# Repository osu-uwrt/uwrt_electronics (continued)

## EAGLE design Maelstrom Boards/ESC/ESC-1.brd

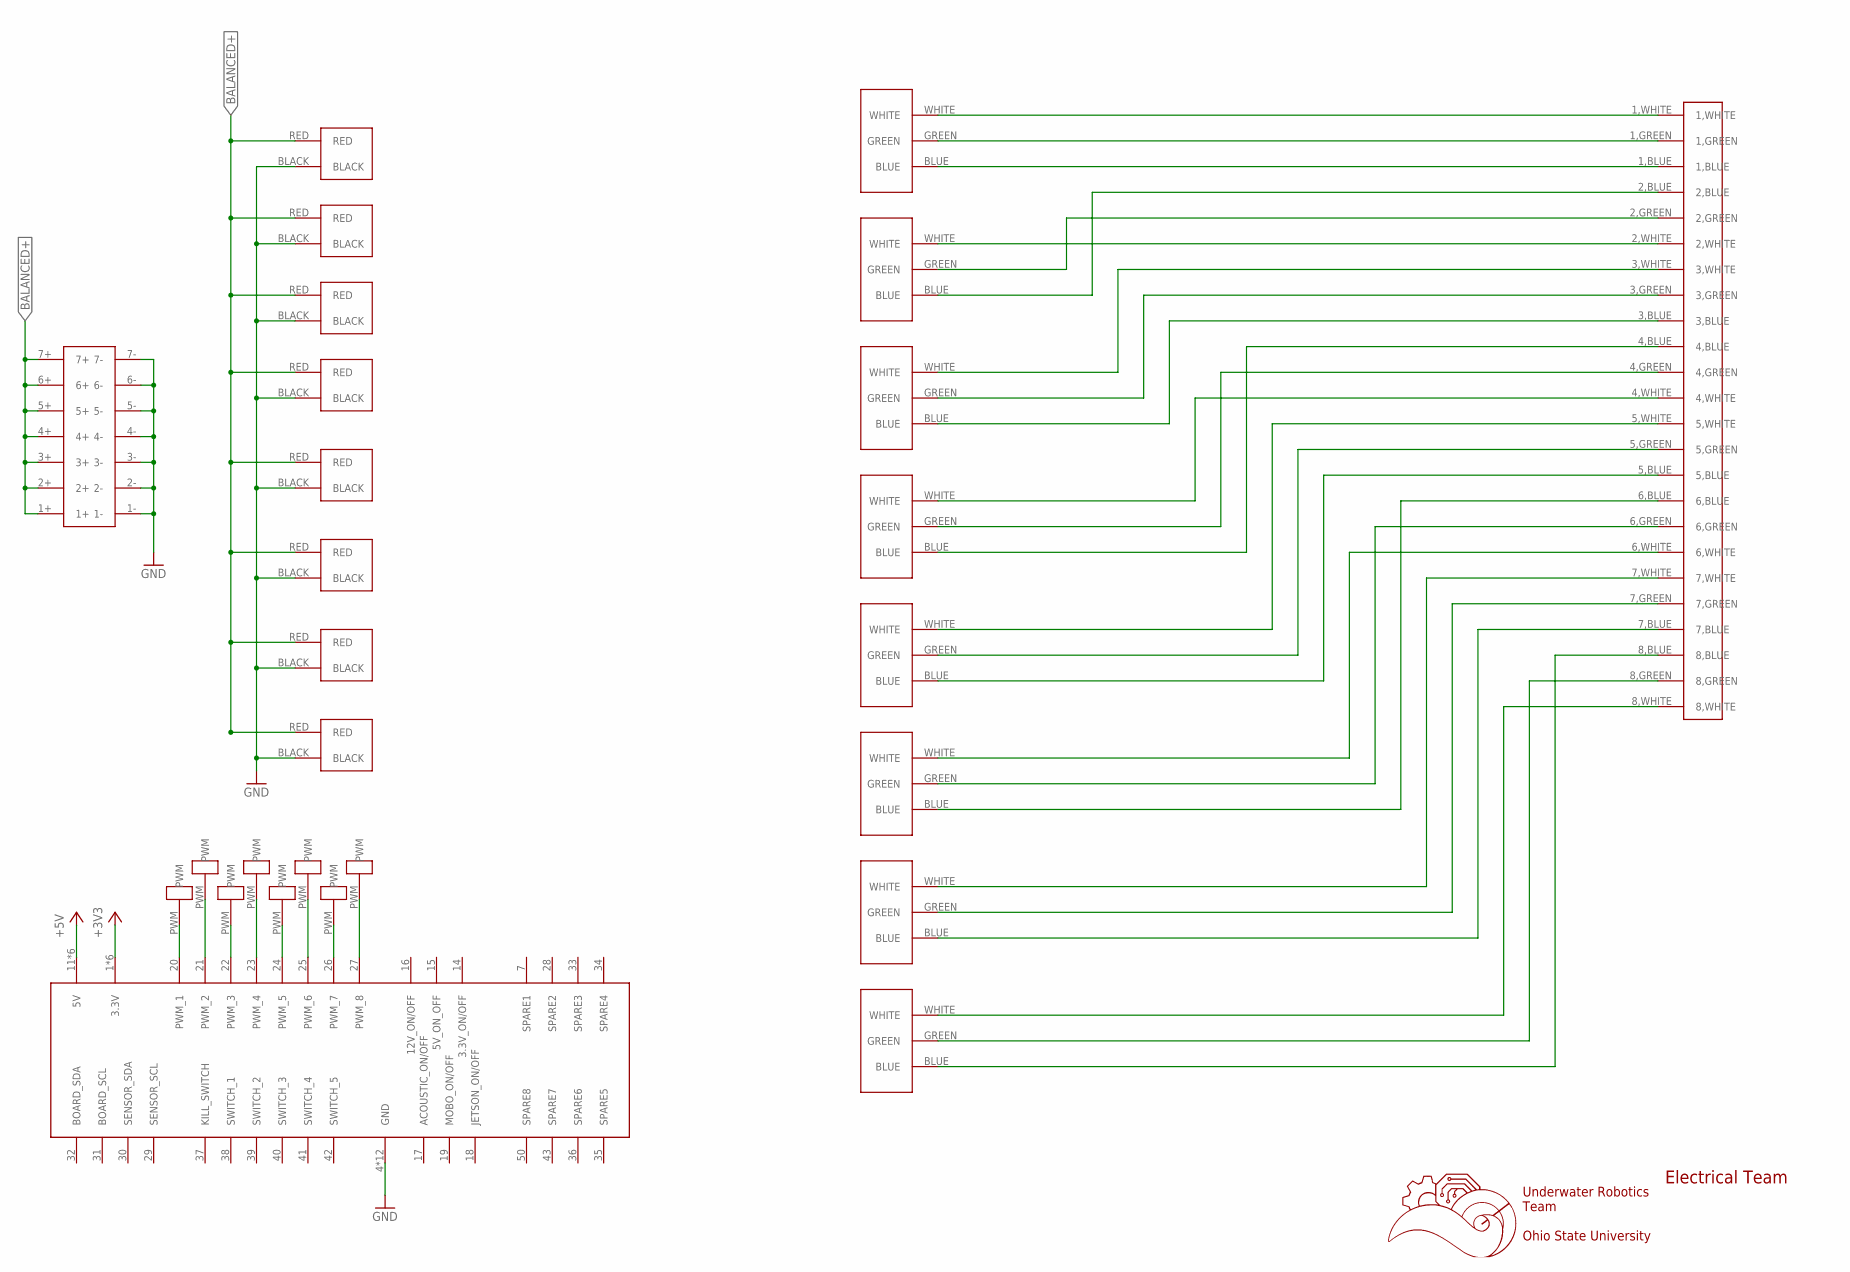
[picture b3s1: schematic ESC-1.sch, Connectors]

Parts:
1, 2, 3, 4, 5, 6, 7, 8: 1711738
U$1: 5530843-EDGE; 5530843-6-BOARDFINGERS
U$2, U$3, U$4, U$5, U$6, U$7, U$8, U$9: 1711725
U$18: 24PINCONVERTER
U$19: 14PIN_VERT
U$20, U$21, U$22, U$23, U$24, U$25, U$26, U$27: MALE1PINHEADER

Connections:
+3V3: U$1.1 (3.3V), U$1.2 (3.3V), U$1.3 (3.3V), U$1.54 (3.3V), U$1.55 (3.3V), U$1.56 (3.3V)
+5V: U$1.11 (5V), U$1.12 (5V), U$1.13 (5V), U$1.44 (5V), U$1.45 (5V), U$1.46 (5V)
BALANCED+: U$2.RED, U$3.RED, U$4.RED, U$5.RED, U$6.RED, U$7.RED, U$8.RED, U$9.RED, U$19.1+, U$19.2+, U$19.3+, U$19.4+, U$19.5+, U$19.6+, U$19.7+
GND: U$1.4 (GND), U$1.5 (GND), U$1.6 (GND), U$1.8 (GND), U$1.9 (GND), U$1.10 (GND), U$1.47 (GND), U$1.48 (GND), U$1.49 (GND), U$1.51 (GND), U$1.52 (GND), U$1.53 (GND), U$2.BLACK, U$3.BLACK, U$4.BLACK, U$5.BLACK, U$6.BLACK, U$7.BLACK, U$8.BLACK, U$9.BLACK, U$19.1-, U$19.2-, U$19.3-, U$19.4-, U$19.5-, U$19.6-, U$19.7-
unnamed: 1.WHITE, U$18.1,WHITE
unnamed: 1.GREEN, U$18.1,GREEN
unnamed: 1.BLUE, U$18.1,BLUE
unnamed: 2.WHITE, U$18.2,WHITE
unnamed: 2.GREEN, U$18.2,GREEN
unnamed: 2.BLUE, U$18.2,BLUE
unnamed: 3.WHITE, U$18.3,WHITE
unnamed: 3.GREEN, U$18.3,GREEN
unnamed: 3.BLUE, U$18.3,BLUE
unnamed: 4.WHITE, U$18.4,WHITE
unnamed: 4.GREEN, U$18.4,GREEN
unnamed: 4.BLUE, U$18.4,BLUE
unnamed: 5.WHITE, U$18.5,WHITE
unnamed: 5.GREEN, U$18.5,GREEN
unnamed: 5.BLUE, U$18.5,BLUE
unnamed: 6.BLUE, U$18.6,BLUE
unnamed: 6.WHITE, U$18.6,WHITE
unnamed: 6.GREEN, U$18.6,GREEN
unnamed: 7.WHITE, U$18.7,WHITE
unnamed: 7.GREEN, U$18.7,GREEN
unnamed: 7.BLUE, U$18.7,BLUE
unnamed: 8.WHITE, U$18.8,WHITE
unnamed: 8.GREEN, U$18.8,GREEN
unnamed: 8.BLUE, U$18.8,BLUE
PWM_1: U$1.20 (PWM_1), U$20.PWM
PWM_2: U$1.21 (PWM_2), U$21.PWM
PWM_3: U$1.22 (PWM_3), U$22.PWM
PWM_4: U$1.23 (PWM_4), U$23.PWM
PWM_5: U$1.24 (PWM_5), U$24.PWM
PWM_6: U$1.25 (PWM_6), U$25.PWM
PWM_7: U$1.26 (PWM_7), U$26.PWM
PWM_8: U$1.27 (PWM_8), U$27.PWM

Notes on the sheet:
Underwater Robotics Team Ohio State University
Electrical Team

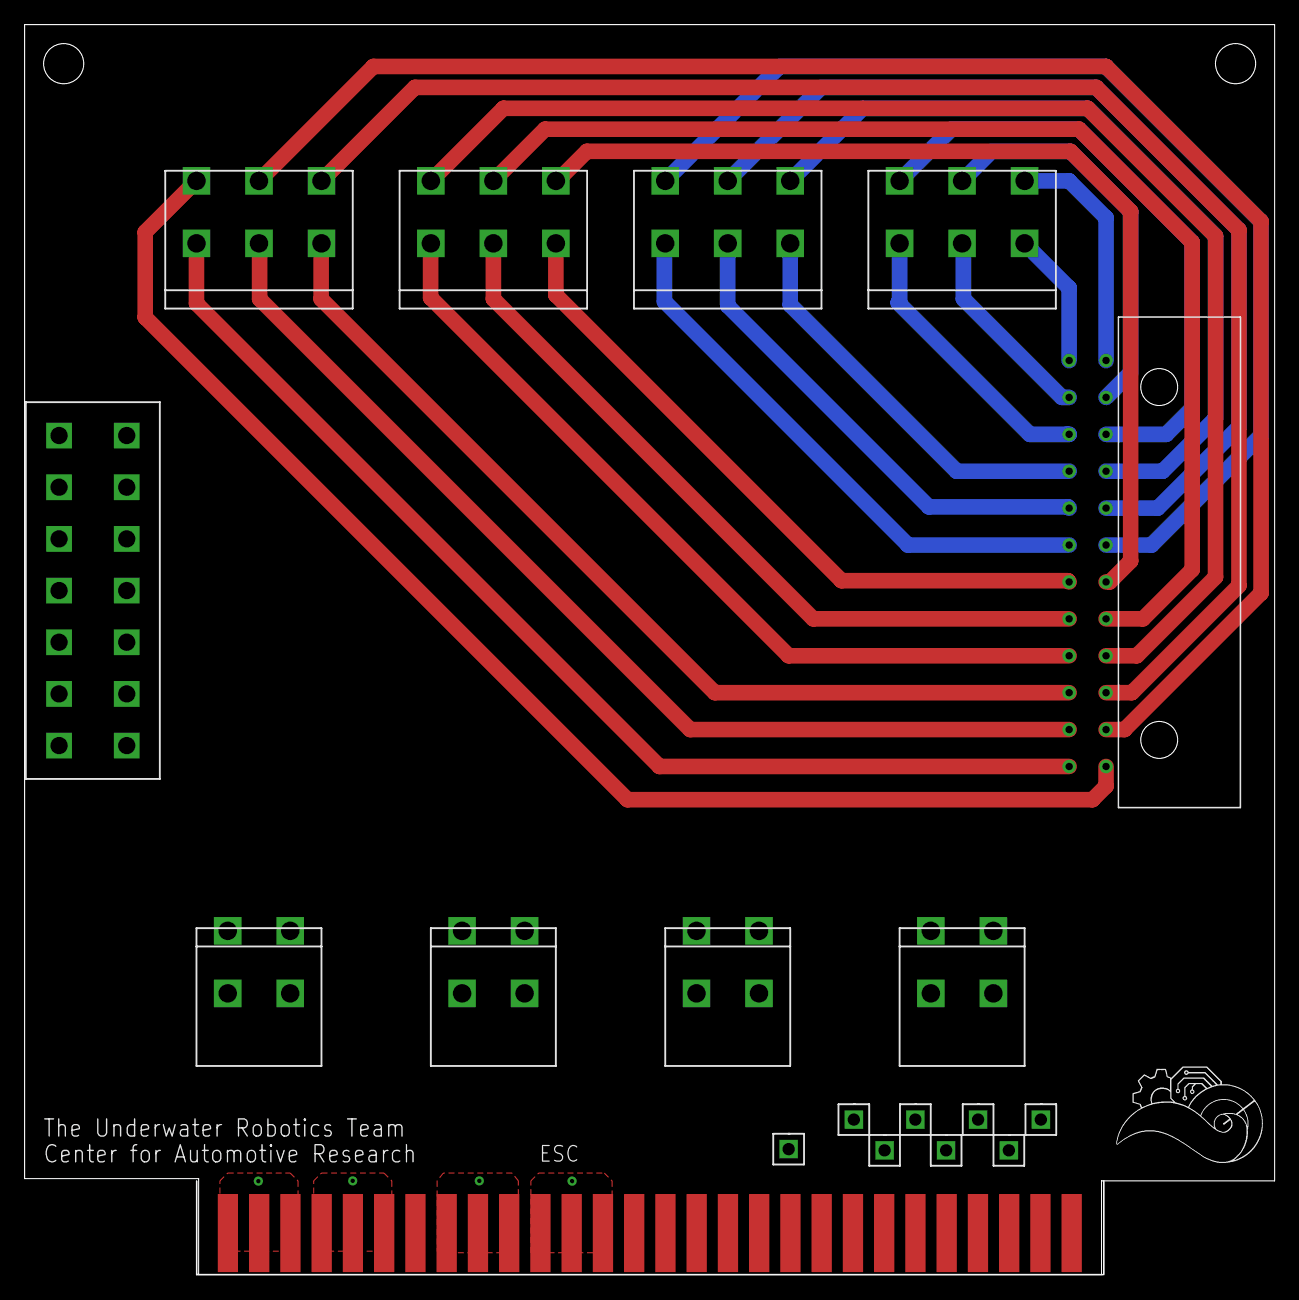
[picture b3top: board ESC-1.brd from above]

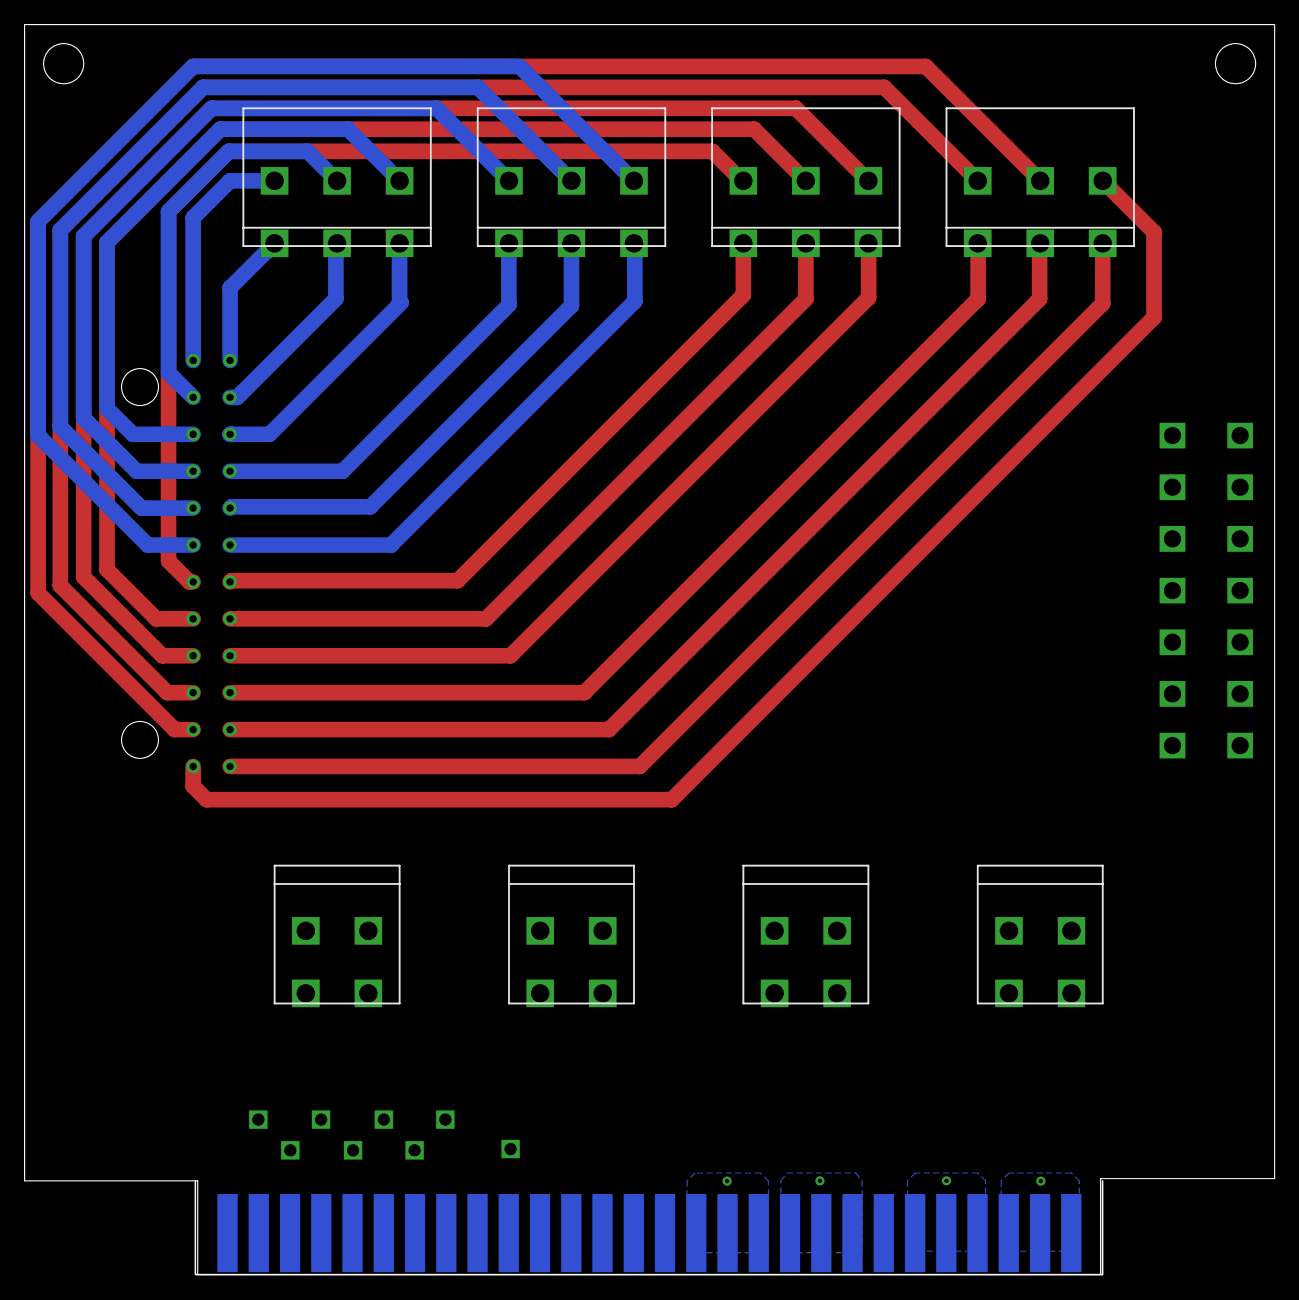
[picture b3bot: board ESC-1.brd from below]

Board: 2 copper layers, 101.6 x 101.6 mm, 27 parts (8 on the bottom side), 36 nets.

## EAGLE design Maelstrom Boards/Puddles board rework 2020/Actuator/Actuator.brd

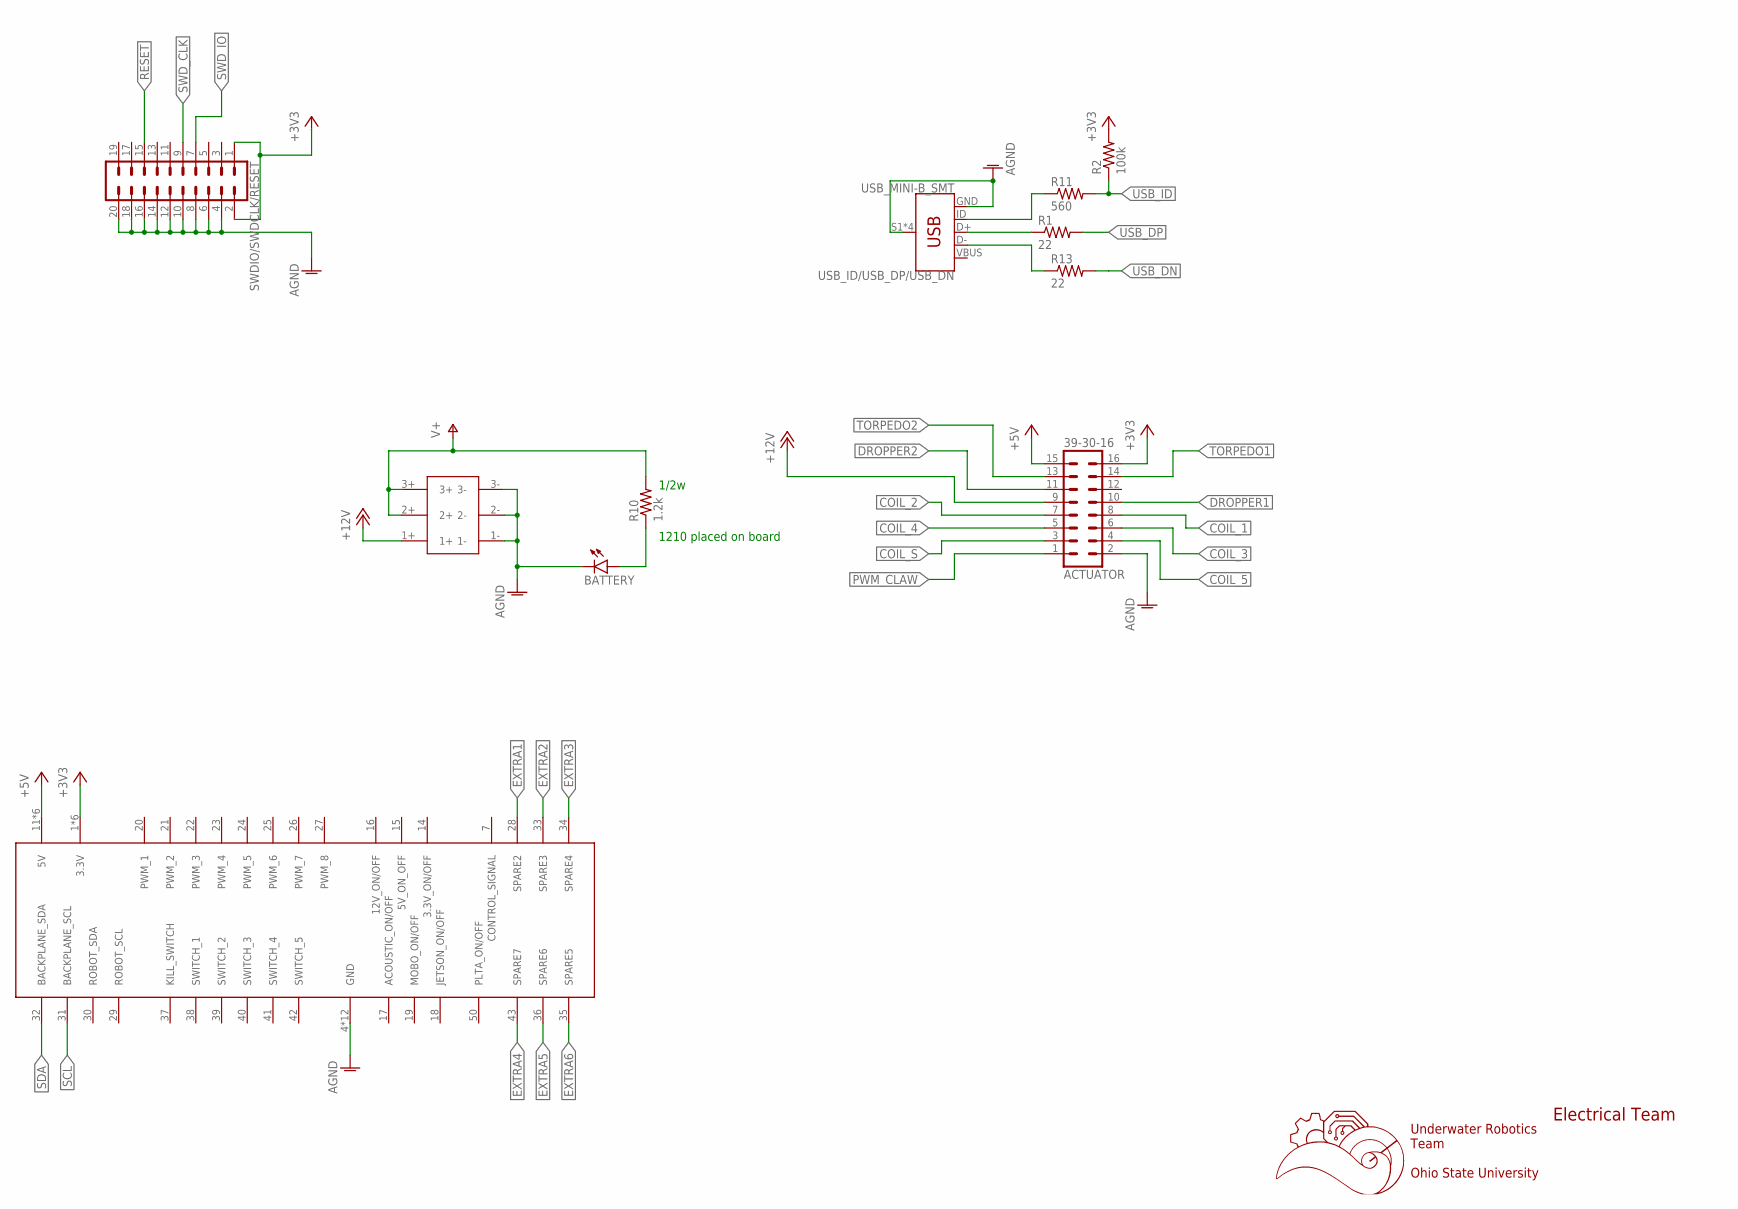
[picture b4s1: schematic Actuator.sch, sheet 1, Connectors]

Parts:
ACTUATOR: 39-30-16; 39-30-?16?
BATTERY: LEDCHIPLED_0603; CHIPLED_0603
R1, R13: 22; R0603
R2: 100k; R0603
R10: 1.2k; R1210
R11: 560; R0603
SWDIO/SWDCLK/RESET: CONN_10X2; 2X10
U$1: 5530843-EDGE; 5530843-6-BOARDFINGERS
U$3: 6PIN-VERT; 6PIN_VERT
USB_ID/USB_DP/USB_DN: USB_MINI-B_SMT; USB-MINIB

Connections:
+3V3: ACTUATOR.16, R2.2, SWDIO/SWDCLK/RESET.1, SWDIO/SWDCLK/RESET.2, U$1.1 (3.3V), U$1.2 (3.3V), U$1.3 (3.3V), U$1.54 (3.3V), U$1.55 (3.3V), U$1.56 (3.3V); also elsewhere on the board
+5V: ACTUATOR.15, U$1.11 (5V), U$1.12 (5V), U$1.13 (5V), U$1.44 (5V), U$1.45 (5V), U$1.46 (5V)
+12V: ACTUATOR.9, U$3.1+; also elsewhere on the board
AGND: ACTUATOR.2, BATTERY.C, SWDIO/SWDCLK/RESET.4, SWDIO/SWDCLK/RESET.6, SWDIO/SWDCLK/RESET.8, SWDIO/SWDCLK/RESET.10, SWDIO/SWDCLK/RESET.12, SWDIO/SWDCLK/RESET.14, SWDIO/SWDCLK/RESET.16, SWDIO/SWDCLK/RESET.18, SWDIO/SWDCLK/RESET.20, U$1.4 (GND), U$1.5 (GND), U$1.6 (GND), U$1.8 (GND), U$1.9 (GND), U$1.10 (GND), U$1.47 (GND), U$1.48 (GND), U$1.49 (GND), U$1.51 (GND), U$1.52 (GND), U$1.53 (GND), U$3.1-, U$3.2-, U$3.3-, USB_ID/USB_DP/USB_DN.GND, USB_ID/USB_DP/USB_DN.S1 (SHIELD), USB_ID/USB_DP/USB_DN.S2 (SHIELD), USB_ID/USB_DP/USB_DN.S3 (SHIELD), USB_ID/USB_DP/USB_DN.S4 (SHIELD); also elsewhere on the board
COIL_1: ACTUATOR.8; also elsewhere on the board
COIL_2: ACTUATOR.7; also elsewhere on the board
COIL_3: ACTUATOR.6; also elsewhere on the board
COIL_4: ACTUATOR.5; also elsewhere on the board
COIL_5: ACTUATOR.4; also elsewhere on the board
COIL_S: ACTUATOR.3; also elsewhere on the board
DROPPER1: ACTUATOR.10; also elsewhere on the board
DROPPER2: ACTUATOR.11; also elsewhere on the board
EXTRA1: U$1.28 (SPARE2); also elsewhere on the board
EXTRA2: U$1.33 (SPARE3); also elsewhere on the board
EXTRA3: U$1.34 (SPARE4); also elsewhere on the board
EXTRA4: U$1.43 (SPARE7); also elsewhere on the board
EXTRA5: U$1.36 (SPARE6); also elsewhere on the board
EXTRA6: U$1.35 (SPARE5); also elsewhere on the board
unnamed: R11.1, USB_ID/USB_DP/USB_DN.ID
unnamed: R1.1, USB_ID/USB_DP/USB_DN.D+
unnamed: R13.1, USB_ID/USB_DP/USB_DN.D-
unnamed: BATTERY.A, R10.1
PWM_CLAW: ACTUATOR.1; also elsewhere on the board
RESET: SWDIO/SWDCLK/RESET.15; also elsewhere on the board
SCL: U$1.31 (BACKPLANE_SCL); also elsewhere on the board
SDA: U$1.32 (BACKPLANE_SDA); also elsewhere on the board
SWD_CLK: SWDIO/SWDCLK/RESET.9; also elsewhere on the board
SWD_IO: SWDIO/SWDCLK/RESET.7; also elsewhere on the board
TORPEDO1: ACTUATOR.14; also elsewhere on the board
TORPEDO2: ACTUATOR.13; also elsewhere on the board
USB_DN: R13.2; also elsewhere on the board
USB_DP: R1.2; also elsewhere on the board
USB_ID: R2.1, R11.2
V+: R10.2, U$3.2+, U$3.3+; also elsewhere on the board
VBUS: USB_ID/USB_DP/USB_DN.VBUS

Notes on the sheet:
Underwater Robotics Team Ohio State University
Electrical Team
1/2w
1210 placed on board

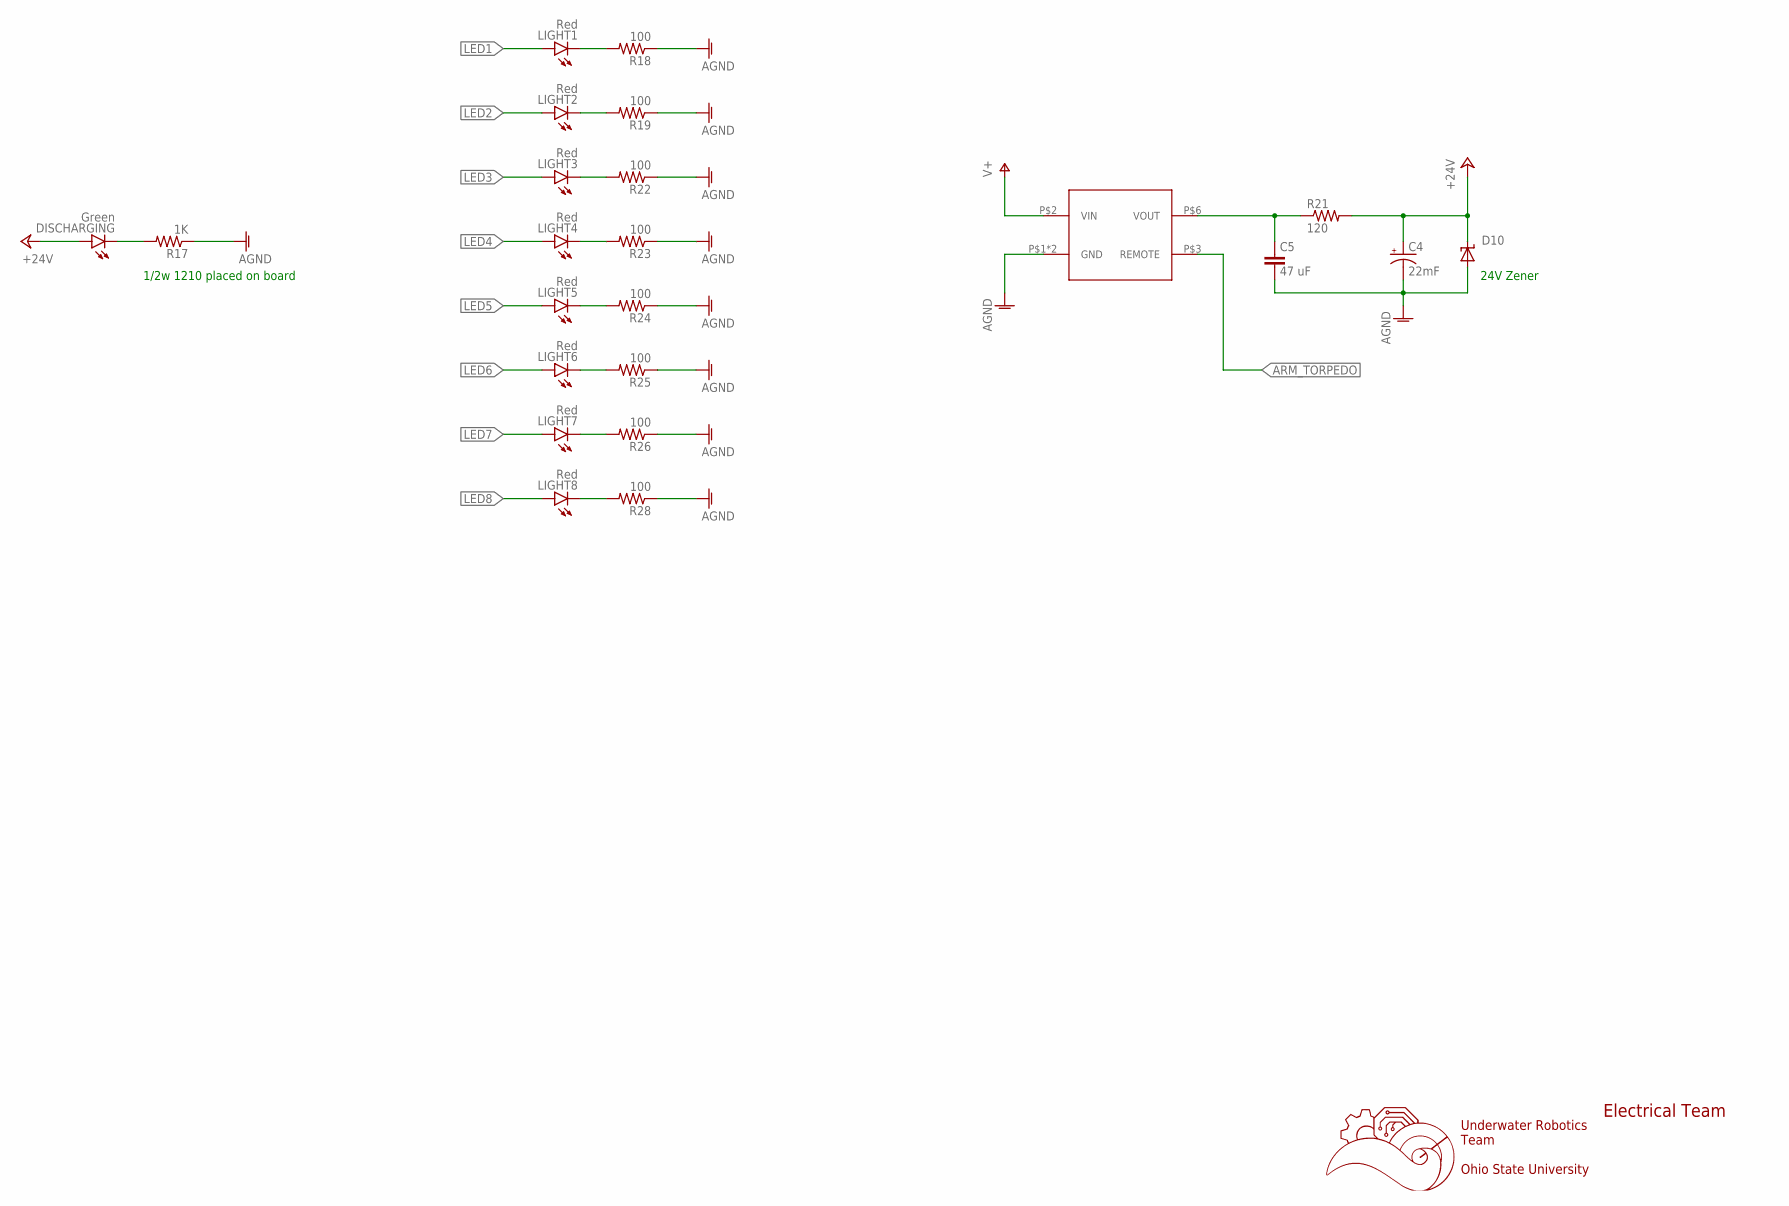
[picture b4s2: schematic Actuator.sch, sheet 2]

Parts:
C4: 22mF; EB30D
C5: 47 uF; C0603
D10: SUPPRESSOR-SMBJ; SMBJ
DISCHARGING: Green; CHIPLED_0603
LIGHT1, LIGHT2, LIGHT3, LIGHT4, LIGHT5, LIGHT6, LIGHT7, LIGHT8: Red; CHIPLED_0603
R17: 1K; R1210
R18, R19, R22, R23, R24, R25, R26, R28: 100; R0603
R21: 120; R6332W
U$6: TMR6-2415

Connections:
+24V: C4.+, D10.C, DISCHARGING.A, R21.2; also elsewhere on the board
AGND: C4.-, C5.2, D10.A, R17.1, R18.1, R19.1, R22.1, R23.1, R24.1, R25.1, R26.1, R28.1, U$6.P$1 (GND), U$6.P$7 (GND); also elsewhere on the board
ARM_TORPEDO: U$6.P$3 (REMOTE); also elsewhere on the board
LED1: LIGHT1.A; also elsewhere on the board
LED2: LIGHT2.A; also elsewhere on the board
LED3: LIGHT3.A; also elsewhere on the board
LED4: LIGHT4.A; also elsewhere on the board
LED5: LIGHT5.A; also elsewhere on the board
LED6: LIGHT6.A; also elsewhere on the board
LED7: LIGHT7.A; also elsewhere on the board
LED8: LIGHT8.A; also elsewhere on the board
unnamed: DISCHARGING.C, R17.2
unnamed: LIGHT1.C, R18.2
unnamed: LIGHT2.C, R19.2
unnamed: LIGHT3.C, R22.2
unnamed: LIGHT4.C, R23.2
unnamed: LIGHT5.C, R24.2
unnamed: LIGHT6.C, R25.2
unnamed: LIGHT7.C, R26.2
unnamed: LIGHT8.C, R28.2
unnamed: C5.1, R21.1, U$6.P$6 (VOUT)
V+: U$6.P$2 (VIN); also elsewhere on the board

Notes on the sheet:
Underwater Robotics Team Ohio State University
Electrical Team
24V Zener
1/2w 1210 placed on board

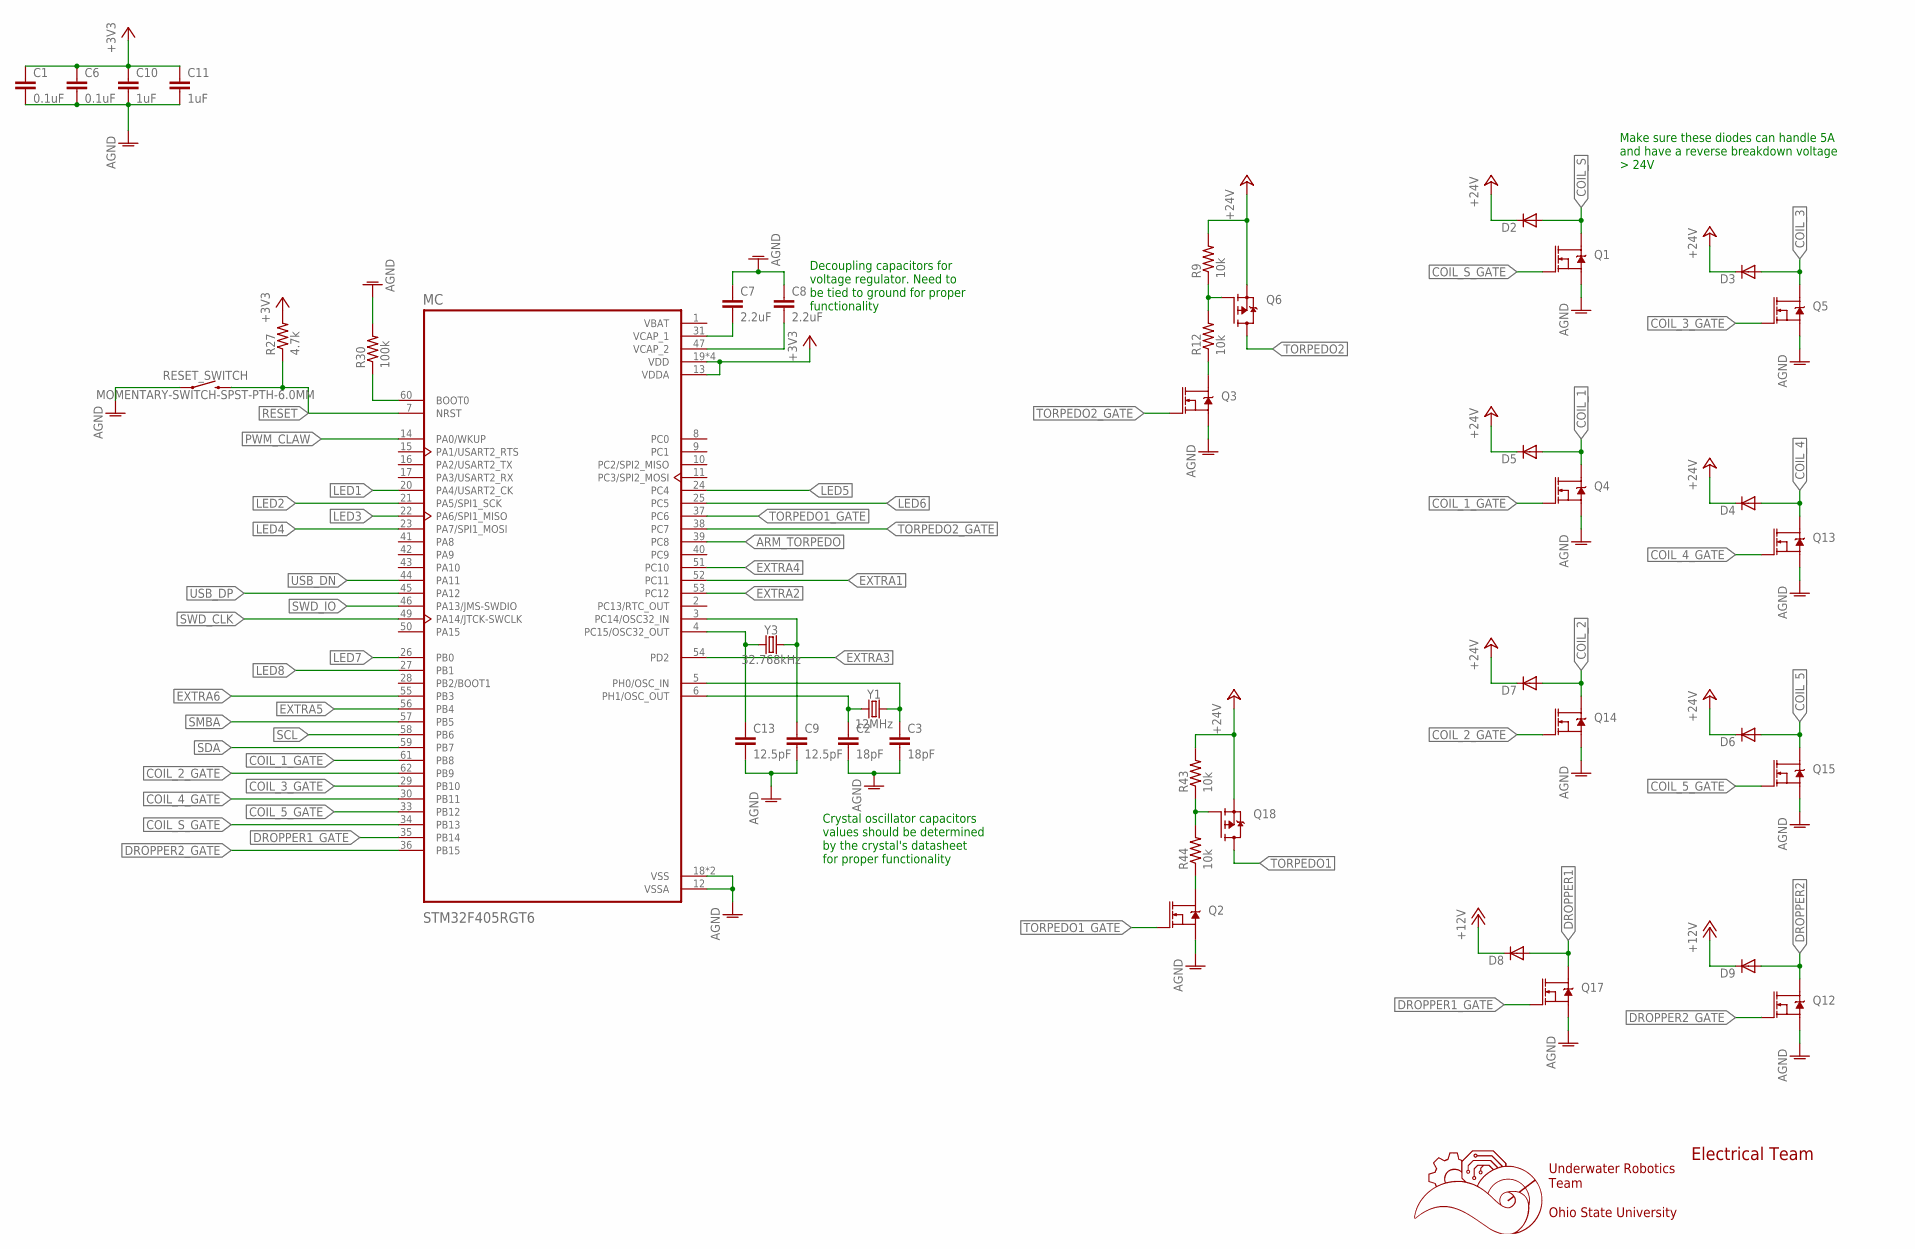
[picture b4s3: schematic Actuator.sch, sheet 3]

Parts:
C1, C6: 0.1uF; C0603
C2, C3: 18pF; C0603
C7, C8: 2.2uF; C0603
C9, C13: 12.5pF; C0603
C10, C11: 1uF; C0603
D2, D3, D4, D5, D6, D7, D8, D9: DIODE-SMB; SMB
MC: STM32F405RGT6; QFP50P1200X1200X160-64N
Q1, Q2, Q3, Q4, Q5, Q12, Q13, Q14, Q15, Q17: MOSFET-NCH-AO3404A; SOT23-3
Q6, Q18: FDD4141TO252; TO252
R9, R12, R43, R44: 10k; R0603
R27: 4.7k; R0603
R30: 100k; R0603
RESET_SWITCH: MOMENTARY-SWITCH-SPST-PTH-6.0MM; TACTILE_SWITCH_PTH_6.0MM
Y1: 12MHz; HC49US
Y3: 32.768kHz; CRYSTAL-SMD-3.2X1.5MM

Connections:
+3V3: C1.1, C6.1, C10.1, C11.1, MC.13 (VDDA), MC.19 (VDD), MC.32 (VDD), MC.48 (VDD), MC.64 (VDD), R27.2; also elsewhere on the board
+12V: D8.C, D9.C; also elsewhere on the board
+24V: D2.C, D3.C, D4.C, D5.C, D6.C, D7.C, Q6.2 (S), Q18.2 (S), R9.2, R43.2; also elsewhere on the board
AGND: C1.2, C2.2, C3.2, C6.2, C7.1, C8.1, C9.2, C10.2, C11.2, C13.2, MC.12 (VSSA), MC.18 (VSS), MC.63 (VSS), Q1.2 (S), Q2.2 (S), Q3.2 (S), Q4.2 (S), Q5.2 (S), Q12.2 (S), Q13.2 (S), Q14.2 (S), Q15.2 (S), Q17.2 (S), R30.2, RESET_SWITCH.1; also elsewhere on the board
ARM_TORPEDO: MC.39 (PC8); also elsewhere on the board
COIL_1: D5.A, Q4.3 (D); also elsewhere on the board
COIL_1_GATE: MC.61 (PB8), Q4.1 (G)
COIL_2: D7.A, Q14.3 (D); also elsewhere on the board
COIL_2_GATE: MC.62 (PB9), Q14.1 (G)
COIL_3: D3.A, Q5.3 (D); also elsewhere on the board
COIL_3_GATE: MC.29 (PB10), Q5.1 (G)
COIL_4: D4.A, Q13.3 (D); also elsewhere on the board
COIL_4_GATE: MC.30 (PB11), Q13.1 (G)
COIL_5: D6.A, Q15.3 (D); also elsewhere on the board
COIL_5_GATE: MC.33 (PB12), Q15.1 (G)
COIL_S: D2.A, Q1.3 (D); also elsewhere on the board
COIL_S_GATE: MC.34 (PB13), Q1.1 (G)
DROPPER1: D8.A, Q17.3 (D); also elsewhere on the board
DROPPER1_GATE: MC.35 (PB14), Q17.1 (G)
DROPPER2: D9.A, Q12.3 (D); also elsewhere on the board
DROPPER2_GATE: MC.36 (PB15), Q12.1 (G)
EXTRA1: MC.52 (PC11); also elsewhere on the board
EXTRA2: MC.53 (PC12); also elsewhere on the board
EXTRA3: MC.54 (PD2); also elsewhere on the board
EXTRA4: MC.51 (PC10); also elsewhere on the board
EXTRA5: MC.56 (PB4); also elsewhere on the board
EXTRA6: MC.55 (PB3); also elsewhere on the board
LED1: MC.20 (PA4/USART2_CK); also elsewhere on the board
LED2: MC.21 (PA5/SPI1_SCK); also elsewhere on the board
LED3: MC.22 (PA6/SPI1_MISO); also elsewhere on the board
LED4: MC.23 (PA7/SPI1_MOSI); also elsewhere on the board
LED5: MC.24 (PC4); also elsewhere on the board
LED6: MC.25 (PC5); also elsewhere on the board
LED7: MC.26 (PB0); also elsewhere on the board
LED8: MC.27 (PB1); also elsewhere on the board
unnamed: C2.1, MC.6 (PH1/OSC_OUT), Y1.1
unnamed: C3.1, MC.5 (PH0/OSC_IN), Y1.2
unnamed: C8.2, MC.47 (VCAP_2)
unnamed: C13.1, MC.4 (PC15/OSC32_OUT), Y3.P$1 (1)
unnamed: C7.2, MC.31 (VCAP_1)
unnamed: Q2.3 (D), R44.1
unnamed: Q18.1 (G), R43.1, R44.2
unnamed: Q6.1 (G), R9.1, R12.2
unnamed: Q3.3 (D), R12.1
unnamed: C9.1, MC.3 (PC14/OSC32_IN), Y3.P$2 (2)
unnamed: MC.60 (BOOT0), R30.1
PWM_CLAW: MC.14 (PA0/WKUP); also elsewhere on the board
RESET: MC.7 (NRST), R27.1, RESET_SWITCH.3 (2); also elsewhere on the board
SCL: MC.58 (PB6); also elsewhere on the board
SDA: MC.59 (PB7); also elsewhere on the board
SMBA: MC.57 (PB5)
SWD_CLK: MC.49 (PA14/JTCK-SWCLK); also elsewhere on the board
SWD_IO: MC.46 (PA13/JMS-SWDIO); also elsewhere on the board
TORPEDO1: Q18.3 (D); also elsewhere on the board
TORPEDO1_GATE: MC.37 (PC6), Q2.1 (G)
TORPEDO2: Q6.3 (D); also elsewhere on the board
TORPEDO2_GATE: MC.38 (PC7), Q3.1 (G)
USB_DN: MC.44 (PA11); also elsewhere on the board
USB_DP: MC.45 (PA12); also elsewhere on the board
VBAT: MC.1 (VBAT)

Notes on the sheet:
Underwater Robotics Team Ohio State University
Electrical Team
Decoupling capacitors for voltage regulator. Need to be tied to ground for proper functionality
Crystal oscillator capacitors values should be determined by the crystal's datasheet for proper functionality
Make sure these diodes can handle 5A and have a reverse breakdown voltage > 24V

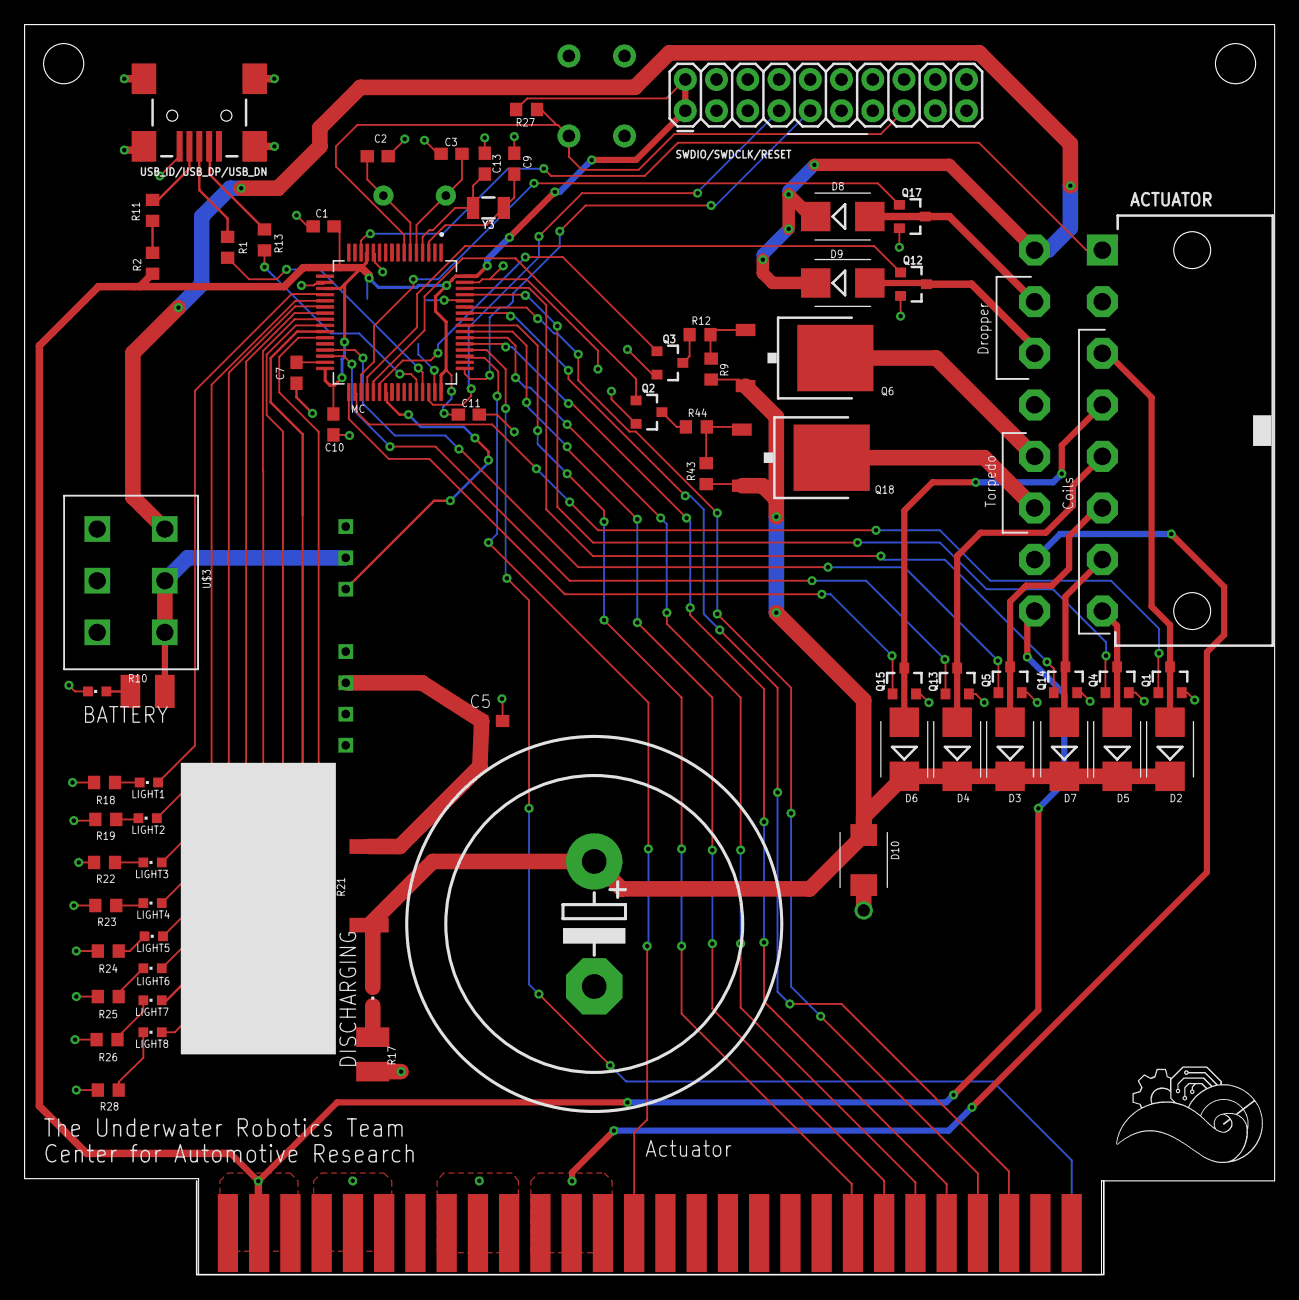
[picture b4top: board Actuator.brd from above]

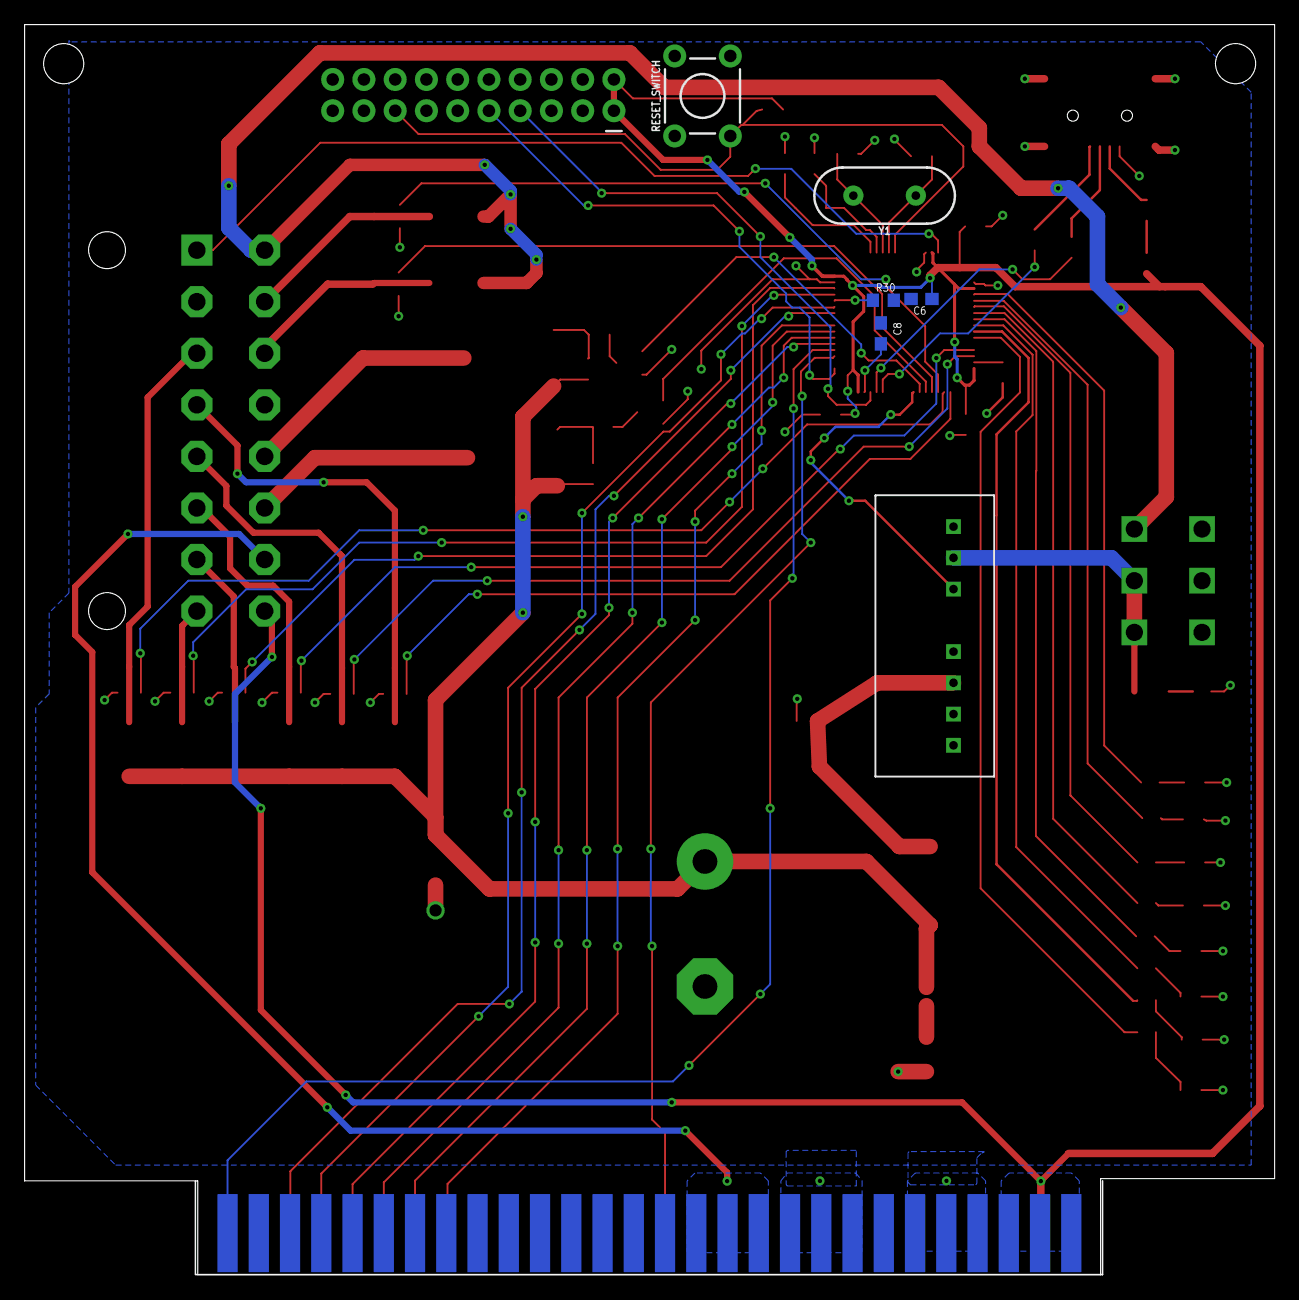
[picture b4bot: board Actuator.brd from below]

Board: 2 copper layers, 101.6 x 101.6 mm, 74 parts (6 on the bottom side), 75 nets.
